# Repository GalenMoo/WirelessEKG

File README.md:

# WirelessEKG
Source Code for Wireless EKG

## Exterior

## Interior

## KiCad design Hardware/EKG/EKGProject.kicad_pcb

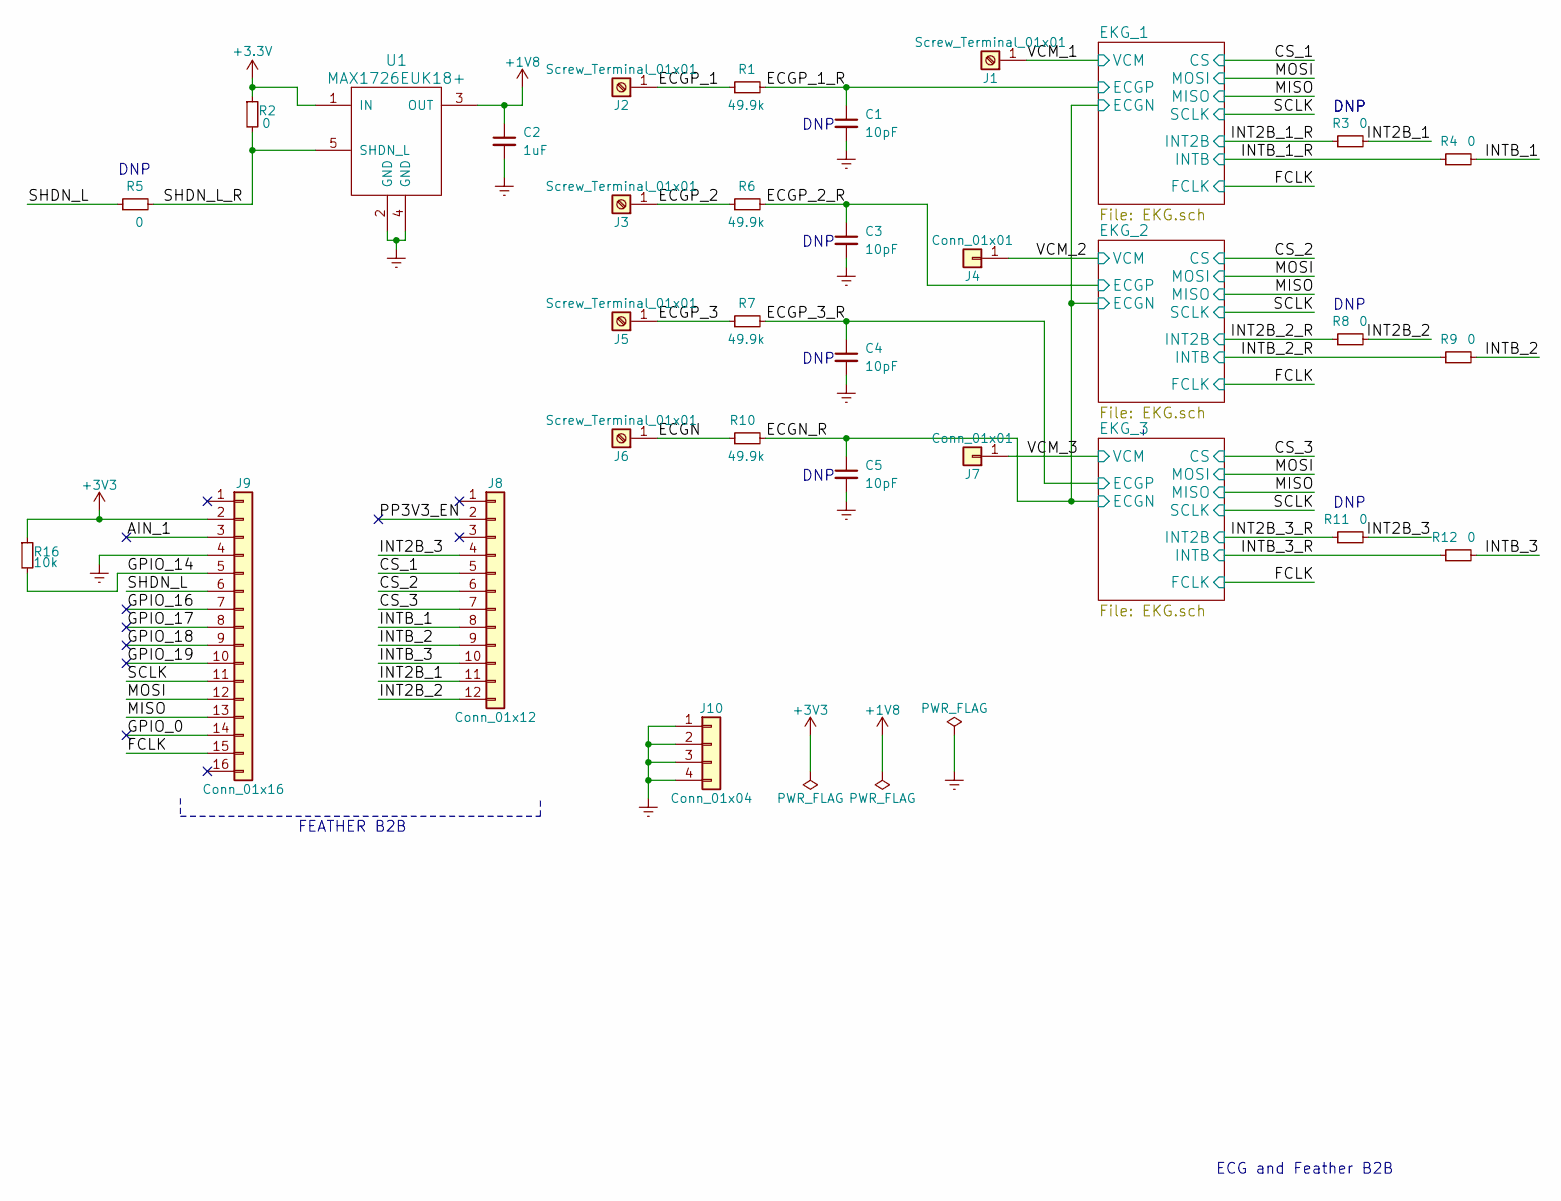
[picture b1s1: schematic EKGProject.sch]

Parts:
C1, C3, C4, C5: 10pF; R_0805_HandSoldering
C2: 1uF; C_0402
J1, J2, J3, J5, J6: Screw_Terminal_01x01; SolderWirePad_single_1-5mmDrill
J4, J7: Conn_01x01; SolderWirePad_single_1-5mmDrill
J8: Conn_01x12; Pin_Header_Straight_1x12_Pitch2.54mm
J9: Conn_01x16; Pin_Header_Straight_1x16_Pitch2.54mm
J10: Conn_01x04; Pin_Header_Straight_1x04_Pitch2.54mm
R1, R6, R7, R10: 49.9k; R_0805_HandSoldering
R2, R3, R4, R5, R8, R9, R11, R12: 0; R_0805_HandSoldering
R16: 10k; R_0805_HandSoldering
U1: MAX1726EUK18+; TSOT-23-5_HandSoldering

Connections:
+1V8: C2.1, U1.3 (OUT); also elsewhere on the board
/AIN_1: J9.3
/CS_1: J8.5; also elsewhere on the board
/CS_2: J8.6; also elsewhere on the board
/CS_3: J8.7; also elsewhere on the board
/ECGN: J6.1, R10.1
/ECGN_R: C5.1, R10.2; also elsewhere on the board
/ECGP_1: J2.1, R1.1
/ECGP_1_R: C1.1, R1.2; also elsewhere on the board
/ECGP_2: J3.1, R6.1
/ECGP_2_R: C3.1, R6.2; also elsewhere on the board
/ECGP_3: J5.1, R7.1
/ECGP_3_R: C4.1, R7.2; also elsewhere on the board
/FCLK: J9.15; also elsewhere on the board
/GPIO_0: J9.14
/GPIO_14: J9.5, R16.2
/GPIO_16: J9.7
/GPIO_17: J9.8
/GPIO_18: J9.9
/GPIO_19: J9.10
/INT2B_1: J8.11, R3.2
/INT2B_1_R: R3.1; also elsewhere on the board
/INT2B_2: J8.12, R8.2
/INT2B_2_R: R8.1; also elsewhere on the board
/INT2B_3: J8.4, R11.2
/INT2B_3_R: R11.1; also elsewhere on the board
/INTB_1: J8.8, R4.2
/INTB_1_R: R4.1; also elsewhere on the board
/INTB_2: J8.9, R9.2
/INTB_2_R: R9.1; also elsewhere on the board
/INTB_3: J8.10, R12.2
/INTB_3_R: R12.1; also elsewhere on the board
/MISO: J9.13; also elsewhere on the board
/MOSI: J9.12; also elsewhere on the board
/PP3V3_EN: J8.2
/SCLK: J9.11; also elsewhere on the board
/SHDN_L: J9.6, R5.1
/SHDN_L_R: R2.2, R5.2, U1.5 (SHDN_L)
/VCM_1: J1.1; also elsewhere on the board
/VCM_2: J4.1; also elsewhere on the board
/VCM_3: J7.1; also elsewhere on the board
Earth: C1.2, C2.2, C3.2, C4.2, C5.2, J9.4, J10.1, J10.2, J10.3, J10.4, U1.2 (GND), U1.4 (GND); also elsewhere on the board

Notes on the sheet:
FEATHER B2B
ECG and Feather B2B
DNP

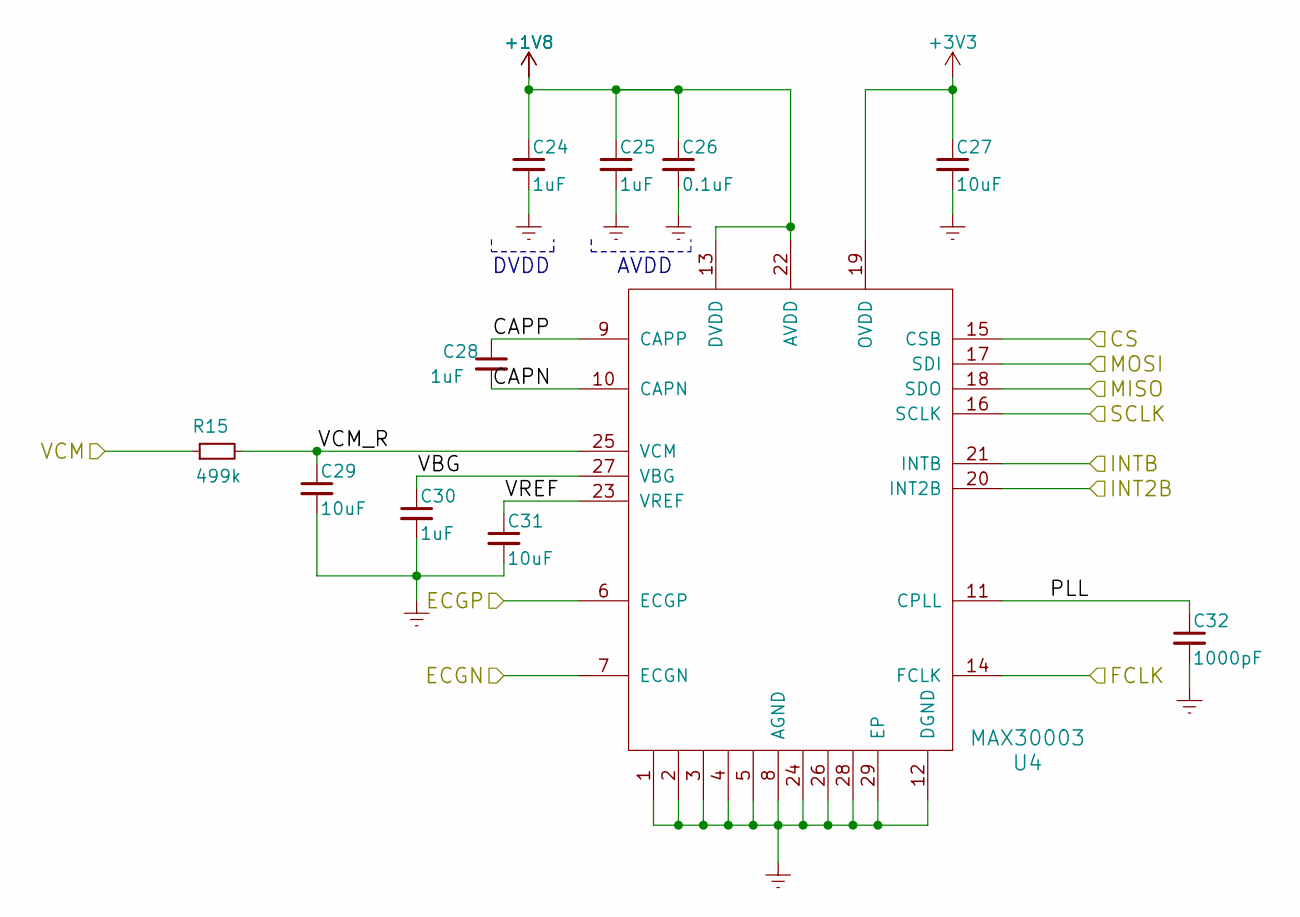
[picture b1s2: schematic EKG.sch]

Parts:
C6, C7, C10, C12: 1uF; C_0402
C8: 0.1uF; C_0402
C9, C11, C13: 10uF; C_0603_HandSoldering
C14: 1000pF; C_0402
R13: 499k; R_0603_HandSoldering
U2: MAX30003; QFN-28-1EP_5x5mm_Pitch0.5mm

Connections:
+1V8: C6.1, C7.1, C8.1, U2.13 (DVDD), U2.22 (AVDD); also elsewhere on the board
/CS_1: U2.15 (CSB); also elsewhere on the board
/ECGN_R: U2.7 (ECGN); also elsewhere on the board
/ECGP_1_R: U2.6 (ECGP); also elsewhere on the board
/EKG_1/CAPN: C10.2, U2.10 (CAPN)
/EKG_1/CAPP: C10.1, U2.9 (CAPP)
/EKG_1/PLL: C14.1, U2.11 (CPLL)
/EKG_1/VBG: C12.1, U2.27 (VBG)
/EKG_1/VCM_R: C11.1, R13.2, U2.25 (VCM)
/EKG_1/VREF: C13.1, U2.23 (VREF)
/FCLK: U2.14 (FCLK); also elsewhere on the board
/INT2B_1_R: U2.20 (INT2B); also elsewhere on the board
/INTB_1_R: U2.21 (INTB); also elsewhere on the board
/MISO: U2.18 (SDO); also elsewhere on the board
/MOSI: U2.17 (SDI); also elsewhere on the board
/SCLK: U2.16 (SCLK); also elsewhere on the board
/VCM_1: R13.1; also elsewhere on the board
Earth: C6.2, C7.2, C8.2, C9.2, C11.2, C12.2, C13.2, C14.2, U2.1, U2.2, U2.3, U2.4, U2.5, U2.8 (AGND), U2.12 (DGND), U2.24, U2.26, U2.28, U2.29 (EP); also elsewhere on the board

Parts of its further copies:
C15, C16, C19, C21, C24, C25, C28, C30: 1uF; C_0402
C17, C26: 0.1uF; C_0402
C18, C20, C22, C27, C29, C31: 10uF; C_0603_HandSoldering
C23, C32: 1000pF; C_0402
R14, R15: 499k; R_0603_HandSoldering
U3, U4: MAX30003; QFN-28-1EP_5x5mm_Pitch0.5mm

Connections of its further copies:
+1V8: C15.1, C16.1, C17.1, C24.1, C25.1, C26.1, U3.13 (DVDD), U3.22 (AVDD), U4.13 (DVDD), U4.22 (AVDD); also elsewhere on the board
/CS_2: U3.15 (CSB); also elsewhere on the board
/CS_3: U4.15 (CSB); also elsewhere on the board
/ECGN_R: U3.7 (ECGN), U4.7 (ECGN); also elsewhere on the board
/ECGP_2_R: U3.6 (ECGP); also elsewhere on the board
/ECGP_3_R: U4.6 (ECGP); also elsewhere on the board
/EKG_2/CAPN: C19.2, U3.10 (CAPN)
/EKG_2/CAPP: C19.1, U3.9 (CAPP)
/EKG_2/PLL: C23.1, U3.11 (CPLL)
/EKG_2/VBG: C21.1, U3.27 (VBG)
/EKG_2/VCM_R: C20.1, R14.2, U3.25 (VCM)
/EKG_2/VREF: C22.1, U3.23 (VREF)
/EKG_3/CAPN: C28.2, U4.10 (CAPN)
/EKG_3/CAPP: C28.1, U4.9 (CAPP)
/EKG_3/PLL: C32.1, U4.11 (CPLL)
/EKG_3/VBG: C30.1, U4.27 (VBG)
/EKG_3/VCM_R: C29.1, R15.2, U4.25 (VCM)
/EKG_3/VREF: C31.1, U4.23 (VREF)
/FCLK: U3.14 (FCLK), U4.14 (FCLK); also elsewhere on the board
/INT2B_2_R: U3.20 (INT2B); also elsewhere on the board
/INT2B_3_R: U4.20 (INT2B); also elsewhere on the board
/INTB_2_R: U3.21 (INTB); also elsewhere on the board
/INTB_3_R: U4.21 (INTB); also elsewhere on the board
/MISO: U3.18 (SDO), U4.18 (SDO); also elsewhere on the board
/MOSI: U3.17 (SDI), U4.17 (SDI); also elsewhere on the board
/SCLK: U3.16 (SCLK), U4.16 (SCLK); also elsewhere on the board
/VCM_2: R14.1; also elsewhere on the board
/VCM_3: R15.1; also elsewhere on the board
Earth: C15.2, C16.2, C17.2, C18.2, C20.2, C21.2, C22.2, C23.2, C24.2, C25.2, C26.2, C27.2, C29.2, C30.2, C31.2, C32.2, U3.1, U3.2, U3.3, U3.4, U3.5, U3.8 (AGND), U3.12 (DGND), U3.24, U3.26, U3.28, U3.29 (EP), U4.1, U4.2, U4.3, U4.4, U4.5, U4.8 (AGND), U4.12 (DGND), U4.24, U4.26, U4.28, U4.29 (EP); also elsewhere on the board

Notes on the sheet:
DVDD
AVDD

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
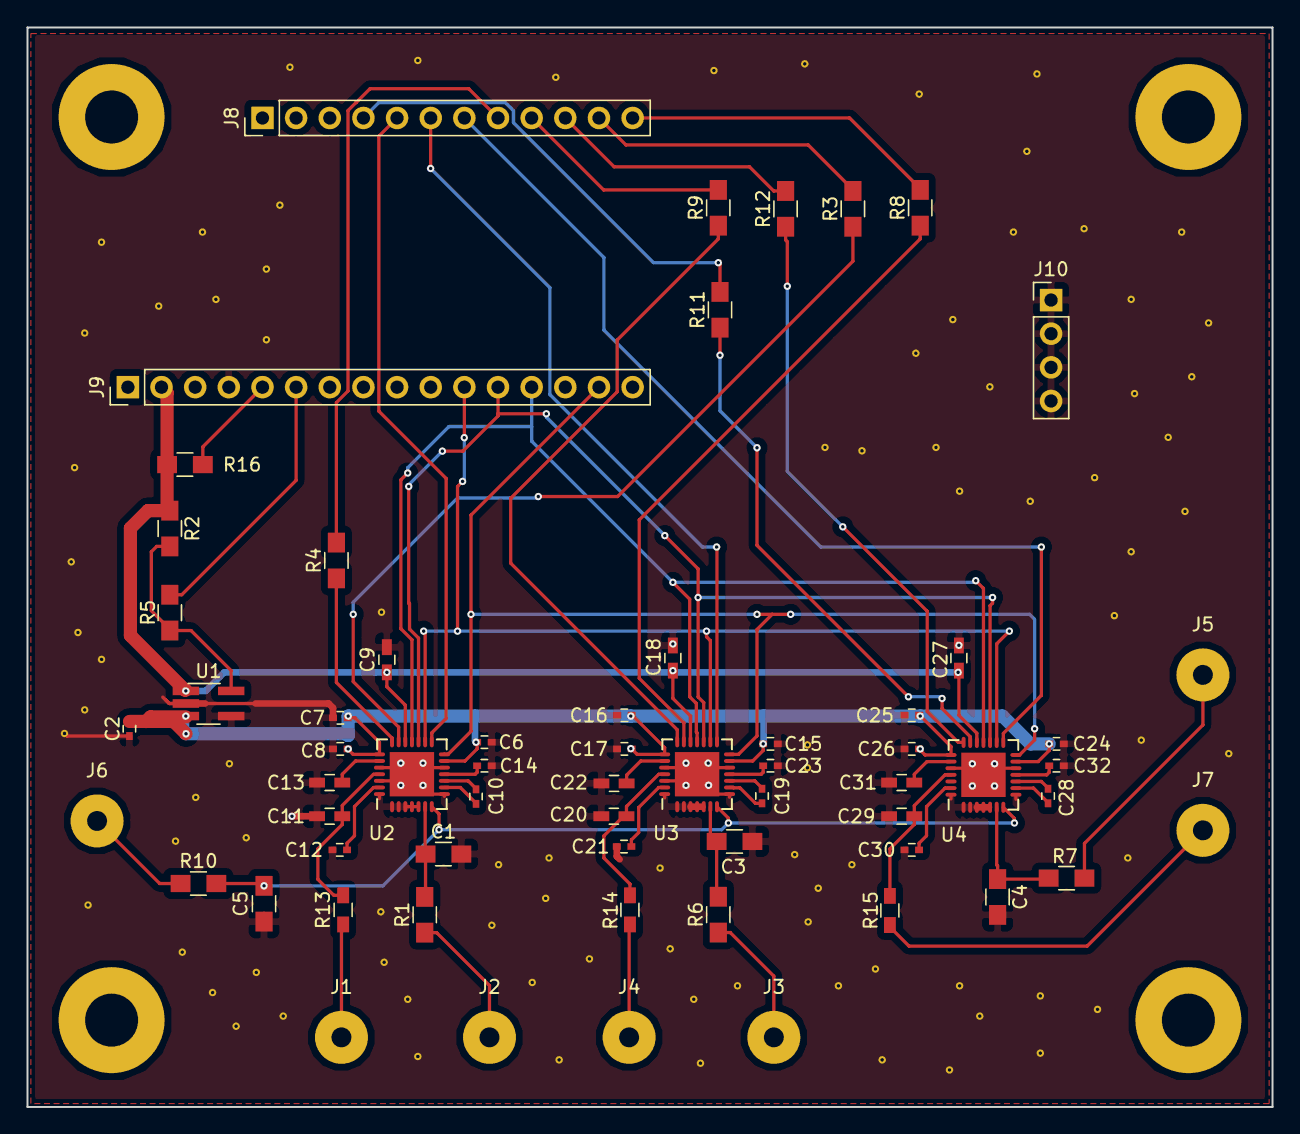
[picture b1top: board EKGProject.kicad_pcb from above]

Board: 2 copper layers, 94.0 x 81.5 mm, 62 parts (0 on the bottom side), 54 nets.

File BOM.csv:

"Id;""Designator"";""Package"";""Quantity"";""Designation"";""Supplier and ref"";",,,,,,,,,,,,,,,,,,,,,,,,,,,,,,,,,,,,,,,,,,,,,,,,,,,,,,,,,,,,,,,,,,,,,,,,,,,,,,,,,,,
"1;""REF**",REF**,REF**,REF**,REF**,REF**,REF**,REF**,REF**,REF**,REF**,REF**,REF**,REF**,REF**,REF**,REF**,REF**,REF**,REF**,REF**,REF**,REF**,REF**,REF**,REF**,REF**,REF**,REF**,REF**,REF**,REF**,REF**,REF**,REF**,REF**,REF**,REF**,REF**,REF**,REF**,REF**,REF**,REF**,REF**,REF**,REF**,REF**,REF**,REF**,REF**,REF**,REF**,REF**,REF**,REF**,REF**,REF**,REF**,REF**,REF**,REF**,REF**,REF**,REF**,REF**,REF**,REF**,REF**,REF**,REF**,REF**,REF**,REF**,REF**,REF**,REF**,REF**,REF**,REF**,REF**,REF**,REF**,"REF**"";""GVIA"";84;""GVIA"";;;"
"2;""REF**",REF**,REF**,"REF**"";""MountingHole_4mm_Pad"";4;""MountingHole_4mm_Pad"";;;",,,,,,,,,,,,,,,,,,,,,,,,,,,,,,,,,,,,,,,,,,,,,,,,,,,,,,,,,,,,,,,,,,,,,,,,,,,,,,,,
"3;""C1",C3,C4,"C5"";""R_0805_HandSoldering"";4;""10pF"";;;",,,,,,,,,,,,,,,,,,,,,,,,,,,,,,,,,,,,,,,,,,,,,,,,,,,,,,,,,,,,,,,,,,,,,,,,,,,,,,,,
"4;""C2",C6,C7,C10,C12,C15,C16,C19,C21,C24,C25,C28,"C30"";""C_0402"";13;""1uF"";;;",,,,,,,,,,,,,,,,,,,,,,,,,,,,,,,,,,,,,,,,,,,,,,,,,,,,,,,,,,,,,,,,,,,,,,,
"5;""C8",C17,"C26"";""C_0402"";3;""0.1uF"";;;",,,,,,,,,,,,,,,,,,,,,,,,,,,,,,,,,,,,,,,,,,,,,,,,,,,,,,,,,,,,,,,,,,,,,,,,,,,,,,,,,
"6;""C9",C11,C13,C18,C20,C22,C27,C29,"C31"";""C_0603_HandSoldering"";9;""10uF"";;;",,,,,,,,,,,,,,,,,,,,,,,,,,,,,,,,,,,,,,,,,,,,,,,,,,,,,,,,,,,,,,,,,,,,,,,,,,,
"7;""C14",C23,"C32"";""C_0402"";3;""1000pF"";;;",,,,,,,,,,,,,,,,,,,,,,,,,,,,,,,,,,,,,,,,,,,,,,,,,,,,,,,,,,,,,,,,,,,,,,,,,,,,,,,,,
"8;""J1",J3,J5,J6,"J2"";""SolderWirePad_single_1-5mmDrill"";5;""Screw_Terminal_01x01"";;;",,,,,,,,,,,,,,,,,,,,,,,,,,,,,,,,,,,,,,,,,,,,,,,,,,,,,,,,,,,,,,,,,,,,,,,,,,,,,,,
"9;""J4","J7"";""SolderWirePad_single_1-5mmDrill"";2;""Conn_01x01"";;;",,,,,,,,,,,,,,,,,,,,,,,,,,,,,,,,,,,,,,,,,,,,,,,,,,,,,,,,,,,,,,,,,,,,,,,,,,,,,,,,,,
"10;""J8"";""Pin_Header_Straight_1x12_Pitch2.54mm"";1;""Conn_01x12"";;;",,,,,,,,,,,,,,,,,,,,,,,,,,,,,,,,,,,,,,,,,,,,,,,,,,,,,,,,,,,,,,,,,,,,,,,,,,,,,,,,,,,
"11;""J9"";""Pin_Header_Straight_1x16_Pitch2.54mm"";1;""Conn_01x16"";;;",,,,,,,,,,,,,,,,,,,,,,,,,,,,,,,,,,,,,,,,,,,,,,,,,,,,,,,,,,,,,,,,,,,,,,,,,,,,,,,,,,,
"12;""J10"";""Pin_Header_Straight_1x04_Pitch2.54mm"";1;""Conn_01x04"";;;",,,,,,,,,,,,,,,,,,,,,,,,,,,,,,,,,,,,,,,,,,,,,,,,,,,,,,,,,,,,,,,,,,,,,,,,,,,,,,,,,,,
"13;""R1",R6,R7,"R10"";""R_0805_HandSoldering"";4;""49.9k"";;;",,,,,,,,,,,,,,,,,,,,,,,,,,,,,,,,,,,,,,,,,,,,,,,,,,,,,,,,,,,,,,,,,,,,,,,,,,,,,,,,
"14;""R2",R3,R4,R5,R8,R9,R11,"R12"";""R_0805_HandSoldering"";8;""0"";;;",,,,,,,,,,,,,,,,,,,,,,,,,,,,,,,,,,,,,,,,,,,,,,,,,,,,,,,,,,,,,,,,,,,,,,,,,,,,
"15;""R13",R14,"R15"";""R_0603_HandSoldering"";3;""499k"";;;",,,,,,,,,,,,,,,,,,,,,,,,,,,,,,,,,,,,,,,,,,,,,,,,,,,,,,,,,,,,,,,,,,,,,,,,,,,,,,,,,
"16;""U1"";""TSOT-23-5_HandSoldering"";1;""MAX1726EUK18+"";;;",,,,,,,,,,,,,,,,,,,,,,,,,,,,,,,,,,,,,,,,,,,,,,,,,,,,,,,,,,,,,,,,,,,,,,,,,,,,,,,,,,,
"17;""U2",U3,"U4"";""QFN-28-1EP_5x5mm_Pitch0.5mm"";3;""MAX30003"";;;",,,,,,,,,,,,,,,,,,,,,,,,,,,,,,,,,,,,,,,,,,,,,,,,,,,,,,,,,,,,,,,,,,,,,,,,,,,,,,,,,
"18;""R16"";""R_0805_HandSoldering"";1;""10k"";;;",,,,,,,,,,,,,,,,,,,,,,,,,,,,,,,,,,,,,,,,,,,,,,,,,,,,,,,,,,,,,,,,,,,,,,,,,,,,,,,,,,,
,,,,,,,,,,,,,,,,,,,,,,,,,,,,,,,,,,,,,,,,,,,,,,,,,,,,,,,,,,,,,,,,,,,,,,,,,,,,,,,,,,,
,,,,,,,,,,,,,,,,,,,,,,,,,,,,,,,,,,,,,,,,,,,,,,,,,,,,,,,,,,,,,,,,,,,,,,,,,,,,,,,,,,,
1,"C1, C3, C4, C5",10pF,805,,,,,,,,,,,,,,,,,,,,,,,,,,,,,,,,,,,,,,,,,,,,,,,,,,,,,,,,,,,,,,,,,,,,,,,,,,,,,,,,
2,"C2, C6, C7, C10, C12, C15, C16, C19, C21, C24, C25, C28, C30",1µF,402,,,,,,,,,,,,,,,,,,,,,,,,,,,,,,,,,,,,,,,,,,,,,,,,,,,,,,,,,,,,,,,,,,,,,,,,,,,,,,,,
3,"C8, C17, C26",0.1µF,402,,,,,,,,,,,,,,,,,,,,,,,,,,,,,,,,,,,,,,,,,,,,,,,,,,,,,,,,,,,,,,,,,,,,,,,,,,,,,,,,
4,"C9, C11, C13, C18, C20, C22, C27, C29, C31",10µF,603,,,,,,,,,,,,,,,,,,,,,,,,,,,,,,,,,,,,,,,,,,,,,,,,,,,,,,,,,,,,,,,,,,,,,,,,,,,,,,,,
5,"C14, C23, C32",1000pF,402,,,,,,,,,,,,,,,,,,,,,,,,,,,,,,,,,,,,,,,,,,,,,,,,,,,,,,,,,,,,,,,,,,,,,,,,,,,,,,,,
6,J8,Conn 1x12,,,,,,,,,,,,,,,,,,,,,,,,,,,,,,,,,,,,,,,,,,,,,,,,,,,,,,,,,,,,,,,,,,,,,,,,,,,,,,,,,
7,J9,Conn 1x16,,,,,,,,,,,,,,,,,,,,,,,,,,,,,,,,,,,,,,,,,,,,,,,,,,,,,,,,,,,,,,,,,,,,,,,,,,,,,,,,,
8,Conn,Conn 1x04,,,,,,,,,,,,,,,,,,,,,,,,,,,,,,,,,,,,,,,,,,,,,,,,,,,,,,,,,,,,,,,,,,,,,,,,,,,,,,,,,
9,"R1, R6, R7, R10",49.9k_,805,,,,,,,,,,,,,,,,,,,,,,,,,,,,,,,,,,,,,,,,,,,,,,,,,,,,,,,,,,,,,,,,,,,,,,,,,,,,,,,,
10,"R2, R3, R4, R5, R8, R9, R11, R12",0_,805,,,,,,,,,,,,,,,,,,,,,,,,,,,,,,,,,,,,,,,,,,,,,,,,,,,,,,,,,,,,,,,,,,,,,,,,,,,,,,,,
11,"R13, R14, R15",499k_,603,,,,,,,,,,,,,,,,,,,,,,,,,,,,,,,,,,,,,,,,,,,,,,,,,,,,,,,,,,,,,,,,,,,,,,,,,,,,,,,,
12,U1,MAX1726EUK18,,,,,,,,,,,,,,,,,,,,,,,,,,,,,,,,,,,,,,,,,,,,,,,,,,,,,,,,,,,,,,,,,,,,,,,,,,,,,,,,,
13,"U2, U3, U4",MAX30003,,,,,,,,,,,,,,,,,,,,,,,,,,,,,,,,,,,,,,,,,,,,,,,,,,,,,,,,,,,,,,,,,,,,,,,,,,,,,,,,,
14,R16,10k_,805,,,,,,,,,,,,,,,,,,,,,,,,,,,,,,,,,,,,,,,,,,,,,,,,,,,,,,,,,,,,,,,,,,,,,,,,,,,,,,,,

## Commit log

2018-04-26 added new stuff
2018-04-26 meowmeowmeow
2018-04-28 refactored code, changed init, created header file along with func file, and more
2018-05-03 Added Hardware folder containing schematic and parts
2018-05-10 Add files via upload
    Updated schematic
    Final version V1
2018-05-21 Added Bluetooth capabilities
2018-05-30 Recent route 5/29
2018-09-09 Added excel sheets
2018-09-24 updated super close finished layout
2018-09-27 hopefully final board layout?
2018-10-08 final final final hopefully
2018-10-08 DFM quick check
2018-10-08 DFM changes again
2018-10-08 one more time DFM lets goooo
2018-10-08 final minus ground vias
2018-10-10 add ground stiching
2018-10-15 upload footprint library
2018-10-15 deleted master
2018-10-15 FINAL
2018-10-15 last adjustments
2018-10-15 Final Revisions
2018-10-15 last BOM update
2021-02-19 pictures
2021-02-19 updated boms
